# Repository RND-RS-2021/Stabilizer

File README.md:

Vehicle Battery Stabilizer for PT. Radiator Springs Indonesia

Contributor: 
*Nur Imam P, Husain Asyari, Maruf Wahyu P*

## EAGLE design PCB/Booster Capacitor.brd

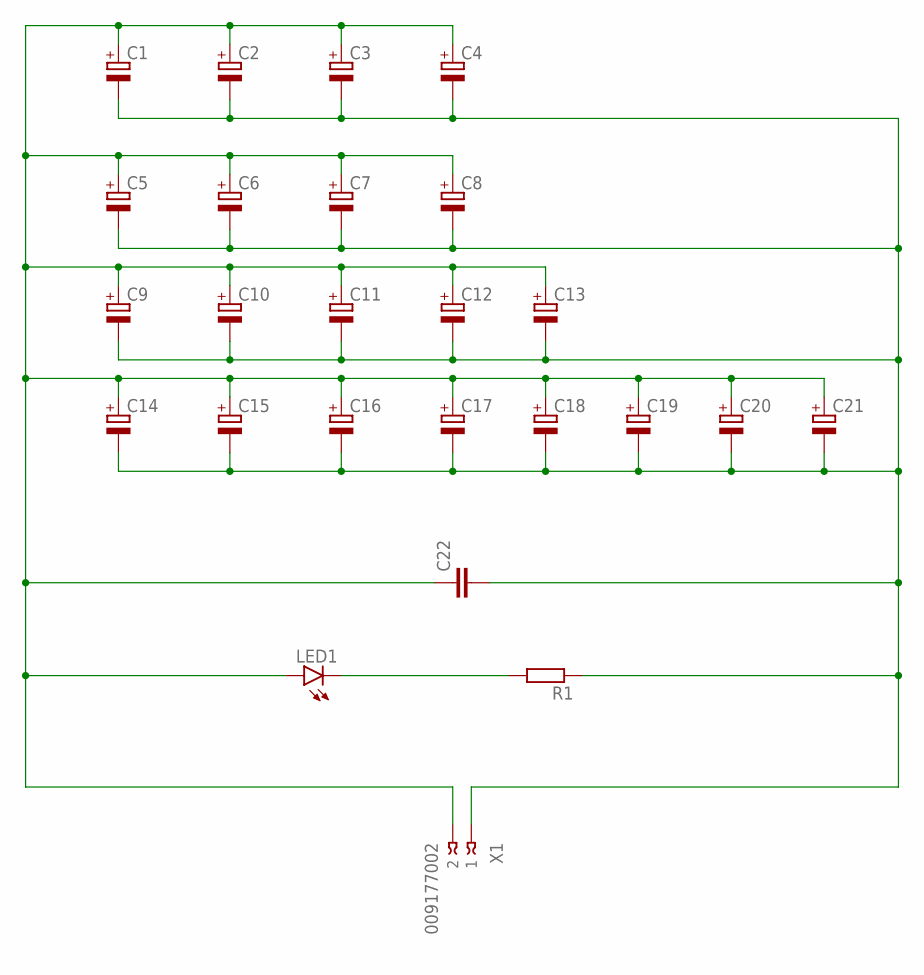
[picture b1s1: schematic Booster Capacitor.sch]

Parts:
C1, C2, C3, C4, C5, C6, C7, C8: CPOL-EUE3.5-8; E3,5-8
C9, C10, C11, C12, C13: CPOL-EUE2.5-7; E2,5-7
C14, C15, C16, C17, C18, C19, C20, C21: CPOL-EUE2.5-6; E2,5-6
C22: C-EU025-025X050; C025-025X050
LED1: LED5MM
R1: R-EU_0207/10; 0207/10
X1: 009177002

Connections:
unnamed: LED1.K (C), R1.2
unnamed: C1.+, C2.+, C3.+, C4.+, C5.+, C6.+, C7.+, C8.+, C9.+, C10.+, C11.+, C12.+, C13.+, C14.+, C15.+, C16.+, C17.+, C18.+, C19.+, C20.+, C21.+, C22.1, LED1.A, X1.2
unnamed: C1.-, C2.-, C3.-, C4.-, C5.-, C6.-, C7.-, C8.-, C9.-, C10.-, C11.-, C12.-, C13.-, C14.-, C15.-, C16.-, C17.-, C18.-, C19.-, C20.-, C21.-, C22.2, R1.1, X1.1

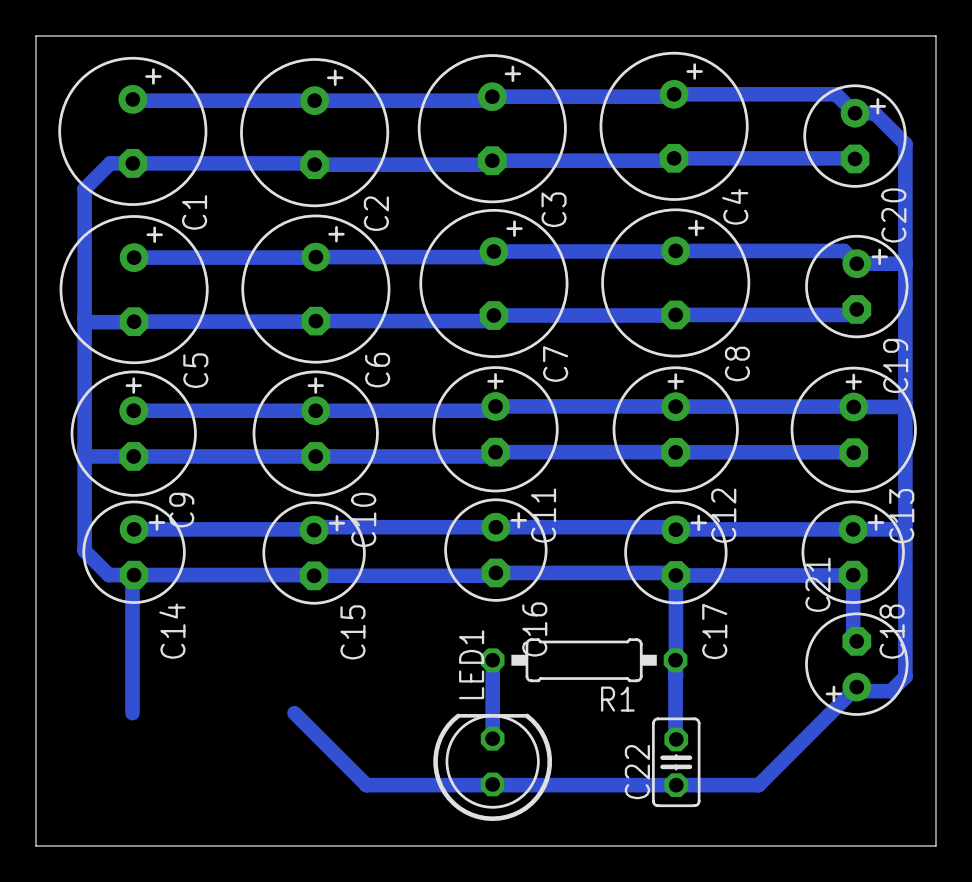
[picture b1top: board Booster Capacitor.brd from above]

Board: 2 copper layers, 50.0 x 45.0 mm, 25 parts (1 on the bottom side), 3 nets.

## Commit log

2021-08-16 Submit
